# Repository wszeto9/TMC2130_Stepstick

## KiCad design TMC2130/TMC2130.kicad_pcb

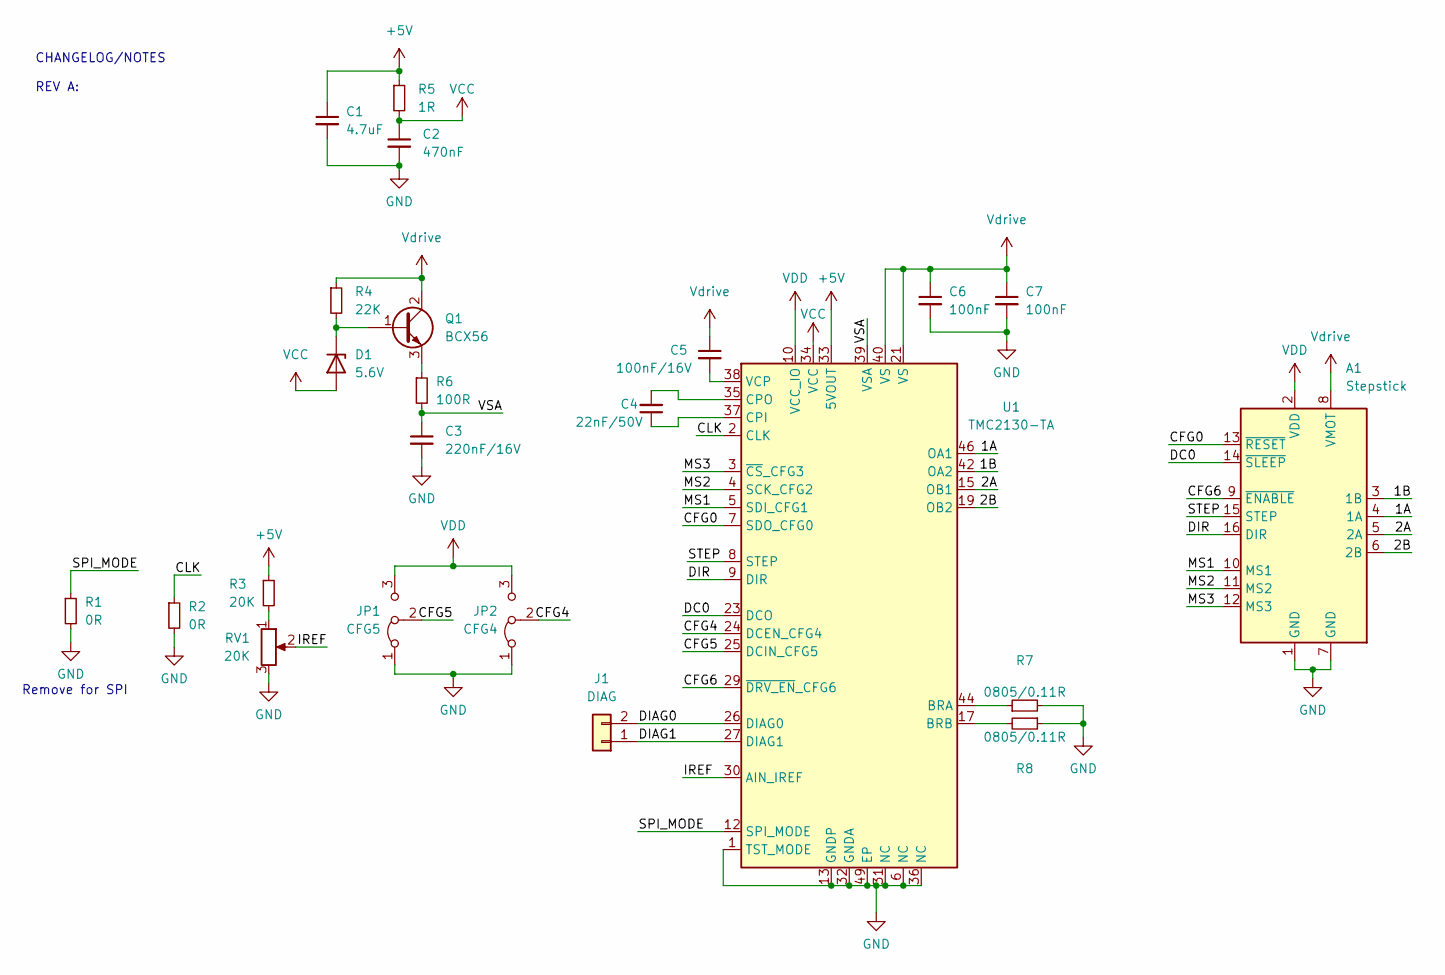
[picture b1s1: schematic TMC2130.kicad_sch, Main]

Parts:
A1: Stepstick; Pololu_Breakout-16_15.2x20.3mm
C1: 4.7uF; C_0402_1005Metric; LCSC C23733
C2: 470nF; C_0402_1005Metric; LCSC C47339
C3: 220nF/16V; C_0402_1005Metric; LCSC C16772
C4: 22nF/50V; C_0402_1005Metric; LCSC C1532
C5: 100nF/16V; C_0402_1005Metric; LCSC C307331
C6, C7: 100nF; C_0402_1005Metric; LCSC C307331
D1: 5.6V; D_MiniMELF; LCSC C8062
J1: DIAG; PinHeader_1x02_P2.54mm_Vertical
JP1: CFG5; SolderJumper-3_P2.0mm_Open_TrianglePad1.0x1.5mm
JP2: CFG4; SolderJumper-3_P2.0mm_Open_TrianglePad1.0x1.5mm
Q1: BCX56; SOT-89-3; LCSC C100026
R1, R2: 0R; R_0402_1005Metric; LCSC C17168
R3: 20K; R_0402_1005Metric; LCSC C25765
R4: 22K; R_0402_1005Metric; LCSC C25768
R5: 1R; R_0402_1005Metric; LCSC C25086
R6: 100R; R_0402_1005Metric; LCSC C25076
R7, R8: 0805/0.11R; R_0805_2012Metric; LCSC C53899
RV1: 20K; Potentiometer_Bourns_TC33X_Vertical
U1: TMC2130-TA; TQFP-48-1EP_7x7mm_P0.5mm_EP5x5mm

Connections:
+5V: C1.1, R3.1, R5.1, U1.33 (5VOUT)
/1A: A1.4 (1A), U1.46 (OA1)
/1B: A1.3 (1B), U1.42 (OA2)
/2A: A1.5 (2A), U1.15 (OB1)
/2B: A1.6 (2B), U1.19 (OB2)
/CFG0: A1.13 (~RESET), U1.7 (SDO_CFG0)
/CFG4: JP2.2 (C), U1.24 (DCEN_CFG4)
/CFG5: JP1.2 (C), U1.25 (DCIN_CFG5)
/CFG6: A1.9 (~ENABLE), U1.29 (~DRV_EN_CFG6)
/CLK: R2.1, U1.2 (CLK)
/DC0: A1.14 (~SLEEP), U1.23 (DCO)
/DIAG0: J1.2, U1.26 (DIAG0)
/DIAG1: J1.1, U1.27 (DIAG1)
/DIR: A1.16 (DIR), U1.9 (DIR)
/IREF: RV1.2, U1.30 (AIN_IREF)
/MS1: A1.10 (MS1), U1.5 (SDI_CFG1)
/MS2: A1.11 (MS2), U1.4 (SCK_CFG2)
/MS3: A1.12 (MS3), U1.3 (~CS_CFG3)
/SPI_MODE: R1.1, U1.12 (SPI_MODE)
/STEP: A1.15 (STEP), U1.8 (STEP)
/VSA: C3.1, R6.2, U1.39 (VSA)
GND: A1.1 (GND), A1.7 (GND), C1.2, C2.2, C3.2, C6.2, C7.2, JP1.1 (A), JP2.1 (A), R1.2, R2.2, R7.2, R8.1, RV1.3, U1.1 (TST_MODE), U1.6 (NC), U1.13 (GNDP), U1.31 (NC), U1.32 (GNDA), U1.36 (NC), U1.48 (GNDP), U1.49 (EP)
unnamed: C4.1, U1.37 (CPI)
unnamed: C4.2, U1.35 (CPO)
unnamed: C5.2, U1.38 (VCP)
unnamed: D1.1 (K), Q1.1 (B), R4.2
unnamed: Q1.3 (E), R6.1
unnamed: R3.2, RV1.1
unnamed: R7.1, U1.44 (BRA)
unnamed: R8.2, U1.17 (BRB)
VCC: C2.1, D1.2 (A), R5.2, U1.34 (VCC)
VDD: A1.2 (VDD), JP1.3 (B), JP2.3 (B), U1.10 (VCC_IO)
Vdrive: A1.8 (VMOT), C5.1, C6.1, C7.1, Q1.2 (C), R4.1, U1.21 (VS), U1.40 (VS)

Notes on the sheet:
Remove for SPI
CHANGELOG/NOTES REV A:

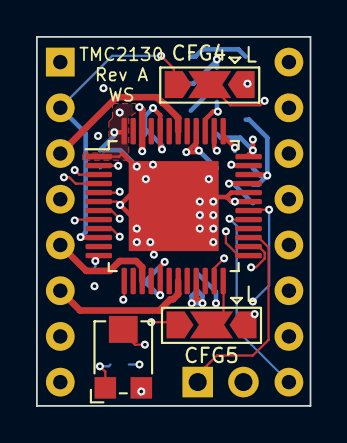
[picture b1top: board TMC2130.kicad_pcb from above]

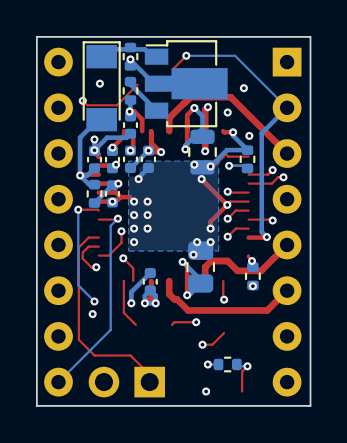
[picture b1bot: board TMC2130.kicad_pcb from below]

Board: 6 copper layers, 15.2 x 20.5 mm, 23 parts (17 on the bottom side), 33 nets.

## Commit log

2022-12-27 changed to 6L
    deleted 2 ground pours to allow for 8L assembly on JLCPCB
